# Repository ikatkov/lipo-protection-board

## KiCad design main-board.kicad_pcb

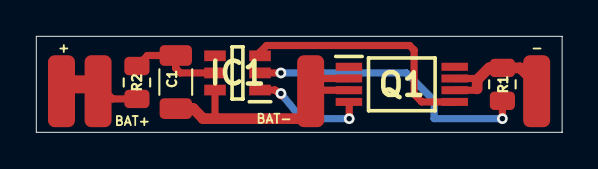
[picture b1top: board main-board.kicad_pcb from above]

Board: 4 copper layers, 29.2 x 5.3 mm, 9 parts (0 on the bottom side), 7 nets.

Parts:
C1: 100n; C_1206_3216Metric
IC1: FS312F-G; SOT95P280X145-6N
J1: BAT-; SolderWirePad_1x01_SMD_1x2mm
J2: POS_OUT; SolderWirePad_1x01_SMD_1x2mm
J3: BAT_POS; SolderWirePad_1x01_SMD_1x2mm
J4: -; SolderWirePad_1x01_SMD_1x2mm
Q1: FS8205A; SOP65P640X120-8N
R1: 1k; R_0805_2012Metric
R2: 100; R_0805_2012Metric

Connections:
BAT_NEG: C1.1, IC1.6 (GND), J1.1, Q1.2 (S1_1), Q1.3 (S1_2)
BAT_POS: J2.1, J3.1, R2.2
unnamed: C1.2, IC1.5 (VCC), R2.1
unnamed: IC1.1 (OD), Q1.4 (G1)
unnamed: IC1.2 (CS), R1.2
unnamed: IC1.3 (OC), Q1.5 (G2)
unnamed: J4.1, Q1.6 (S2_1), Q1.7 (S2_2), R1.1

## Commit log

2022-10-28 Rectangular-board
2022-10-28 minor
2022-10-28 images
2022-10-28 add schematic
